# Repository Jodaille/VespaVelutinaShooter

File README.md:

# Vespa Velutina Shooter

## Objectif du PCB

- Détection acoustique du vol de frelon (micro sur ADS1115)
- Localisation du point le plus sombre de l'image prise avec la caméra de l'ESP32-Cam
- balayage de la zone avec le pan-tilt (2 servos controllés par PCA9685)
- détection du frelon par capteur laser (Dout sur ADS1115)
- collage du relais (PCA9685)
- ouverture electrovanne d'air comprimé
- sauvegarde de l'image sur la carte Sd
- projection d'une bille d'airsoft
- ré-enclenchement d'une bille

## Composants

- ESP-32 Cam
http://www.ai-thinker.com/pro_view-24.html

- Adafruit 16-Channel 12-bit PWM/Servo Driver - I2C interface - PCA9685
https://www.adafruit.com/product/815

- ADS1115 16-Bit ADC - 4 Channel with Programmable Gain Amplifier
https://www.adafruit.com/product/1085

- Waveshare Laser Sensor
https://www.waveshare.com/laser-sensor.htm

- Electret Microphone Amplifier - MAX9814 with Auto Gain Control
https://www.adafruit.com/product/1713

## Composants complémentaires

- horloge RTC: Adafruit DS3231 Precision RTC Breakout
https://www.adafruit.com/product/3013

Permttrait:
- Activation pendant la journée
- conserver l'heure des détections (recouper avec un enregistrement video par exemple)

# PCB prévisualisation

# Projets liés/utilisés

Le détecteur de Bernard:

https://github.com/Barrois/Detecteur-ESP32-Cam-Blob-Detector

Enregistrements audio de Vespa Velutina:

https://github.com/Jodaille/VespaVelutinaAudioRecords

Merci à EloquentArduino pour son projet de détection dans l'image avec un ESP-32 !

https://github.com/eloquentarduino/EloquentArduino

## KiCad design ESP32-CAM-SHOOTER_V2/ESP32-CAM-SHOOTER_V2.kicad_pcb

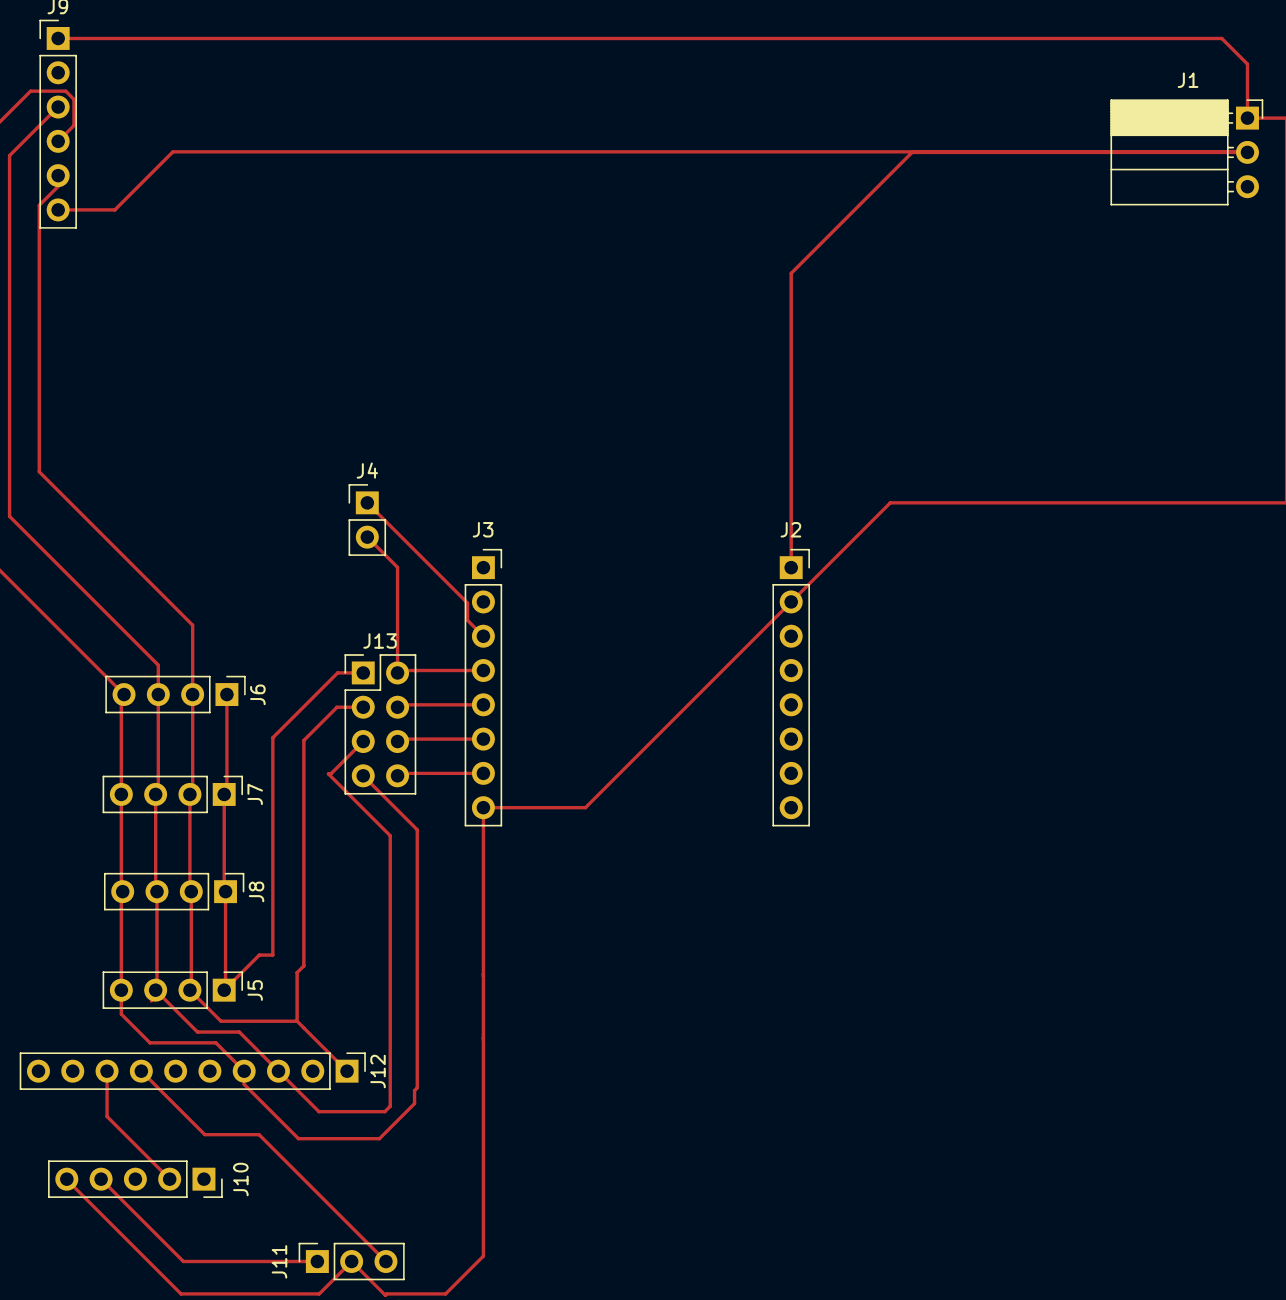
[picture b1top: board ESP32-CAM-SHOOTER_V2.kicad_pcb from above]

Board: 2 copper layers, 13 parts (0 on the bottom side), 12 nets.

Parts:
J1: Alimentation 5V; PinSocket_1x03_P2.54mm_Horizontal
J2: ESP32 Header1; PinSocket_1x08_P2.54mm_Vertical
J3: ESP32 Header2; PinSocket_1x08_P2.54mm_Vertical
J4: Flash mode; PinHeader_1x02_P2.54mm_Vertical
J5: I2C SX1509; PinHeader_1x04_P2.54mm_Vertical
J6: I2C DS3231 RTC; PinHeader_1x04_P2.54mm_Vertical
J7: I2C ssd1306 Screen; PinHeader_1x04_P2.54mm_Vertical
J8: I2C Autre; PinHeader_1x04_P2.54mm_Vertical
J9: PCA9685; PinHeader_1x06_P2.54mm_Vertical
J10: MAX9814; PinSocket_1x05_P2.54mm_Vertical
J11: Laser sensor; PinSocket_1x03_P2.54mm_Vertical
J12: ADS1115; PinHeader_1x10_P2.54mm_Vertical
J13: Switch Série/I2C; PinHeader_2x04_P2.54mm_Vertical

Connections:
GND: J1.1, J2.2, J3.4, J3.8, J4.2, J5.1, J6.1, J7.1, J8.1, J9.1, J10.5, J11.2, J12.2, J13.1, J13.2
unnamed: J3.3, J4.1
unnamed: J10.2, J12.8
unnamed: J10.4, J11.1
unnamed: J11.3, J12.7
unnamed: J5.2, J6.2, J7.2, J8.2, J9.5, J12.1, J13.3
unnamed: J5.3, J6.3, J7.3, J8.3, J9.3, J12.3, J13.5
unnamed: J5.4, J6.4, J7.4, J8.4, J9.4, J12.4, J13.7
unnamed: J3.5, J13.4
unnamed: J3.6, J13.6
unnamed: J3.7, J13.8
VCC: J1.2, J2.1, J9.6

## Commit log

2021-01-29 first version 100x100mm
2021-01-29 add headers for breakout
2021-01-29 export schema svg
2021-01-30 add pca footprint
2021-01-31 Ajout liste des composants
2021-01-31 Ajout liens projets
2021-01-31 Corrections/précisions
2021-02-01 add v2
2021-02-01 add rendered v0.3
